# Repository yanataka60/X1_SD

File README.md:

# SHARP X1、X1turboにSD-CARDからロード、セーブ機能

　X1、X1turbo、X1turboZでSD-CARDからのアプリケーション起動とBASICなどのアプリケーションからSD-CARDへのロード、セーブを実現するものです。

　電源ONで起動するSD対応LauncherからはF又はLコマンドでSDからアプリケーションをLOAD実行ができます。

　LOAD実行範囲は、0000h～FF1Fhです。アプリケーション、ゲームを起動させるにはほぼ問題ないと思います。

　起動出来るのは、１段でロードできるCMTアプリケーションのみです。多段ロードで起動するCMTアプリケーションには対応していません。

　アプリケーション中でのSD-CARDとのロード、セーブについては、アプリケーションごとにSD-CARD対応化を行う必要があり、現在対応できているものは以下のとおりです。

|アプリケーション名|掲載誌|
| ------------ | ------------ |
|BASIC CZ-8CB01||
|S-OS SWORD TAPE版|Oh!MZ '86/2月号 '87/3,'89/2再掲載|
|TTLインタプリタ|Oh!MZ '84/10月号|
|EDAS for X1|月刊I/O '84/6月号|
|エディタ・アセンブラ|渡辺英行・沼倉　均共著「マシン語プログラミング入門」|
|Stellarコンパイラ|渡辺英行、高橋秀樹共著「X1ハイテックファイル」|

　X1turbo、X1turboZで利用するときは、RESOLUTIONスイッチを「STANDARD」にしてください。

　X1_SDはX1用アプリケーションを対象としており、X1_SD LauncherもX1用BASICからMONITOR部分を切り出して利用しています。

　なお、Arduino、ROMへ書き込むための機器が別途必要となります。

## 回路図
[X1_SD](https://github.com/yanataka60/X1_SD/blob/main/Kicad/X1_SD.pdf)

## 部品
|番号|品名|数量|備考|
| ------------ | ------------ | ------------ | ------------ |
||J2、J3のいずれか|||
|J2|Micro_SD_Card_Kit|1|秋月電子通商 AE-microSD-LLCNV (注1)|
|J3|MicroSD Card Adapter|1|Arduino等に使われる5V電源に対応したもの (注3)|
|J4|2x22Pinコネクタ|1|秋月電子通商 PH-2x40SGなど 拡張スロットの無いCZ-800に接続するときに必要です|
|J5|2x25Pinコネクタ|1|秋月電子通商 PH-2x40SGなど CZ-801に接続するときに必要です|
|J6|1x2Pinコネクタ|1|秋月電子通商 PH-1x40RG(2)など|
|R1、R2|1kΩ|2||
|U1|74LS04|1||
|U2|74LS30|1||
|U3|74LS10|1||
|U4、U7|74LS27|2||
|U5、U8|74LS273|2||
|U6、U9|74LS32|2||
|U10|74LS139|1||
|U11|74LS541|1||
|U12|8255|1||
|U13|27512/27C512相当品|1||
|U14|Arduino_Pro_Mini_5V|1|Atmega328版を使用 168版は不可。(注2)|
|C1、C3-C14|積層セラミックコンデンサ 0.1uF|6||
|C2|電解コンデンサ 16v100uF|1||
|S1|3Pスライドスイッチ|1|秋月電子通商 SS12D01G4など|
||ピンヘッダ|2Pin分|Arduino_Pro_MiniにはA4、A5用のピンヘッダが付いていないため別途調達が必要です 秋月電子通商 PH-1x40SGなど|
||ピンソケット(任意)|26Pin分|Arduino_Pro_Miniを取り外し可能としたい場合に調達します 秋月電子通商 FHU-1x42SGなど|
||2.54mmピッチ2x25Pinフラットケーブル|1|拡張スロットの無いCZ-800、CZ-801に接続するときに必要です(注4)|

　　　注1)秋月電子通商　AE-microSD-LLCNVのJ1ジャンパはショートしてください。

　　　注2)Arduino Pro MiniはA4、A5ピンも使っています。

　　　注3)Arduino等に使われる5V電源に対応したMicroSD Card Adapterも正しく信号を繋げば使えるとご報告いただきました。

　　　注4)拡張スロットの無いCZ-800に接続するときには本来2.54mmピッチ2x22Pinフラットケーブルですが、手に入りにくいので2.54mmピッチ2x25Pinフラットケーブルでも接続できます。CZ-801の接続には2.54mmピッチ2x25Pinフラットケーブルが必要です。

### MicroSD Card Adapterを使う
J3に取り付けます。

MicroSD Card Adapterについているピンヘッダを除去してハンダ付けするのが一番確実ですが、J3の穴にMicroSD Card Adapterをぴったりと押しつけ、裏から多めにハンダを流し込むことでハンダ付けをする方法もあります。なお、この方法の時にはしっかりハンダ付けが出来たかテスターで導通を確認しておいた方が安心です。

ハンダ付けに自信のない方はJ2の秋月電子通商　AE-microSD-LLCNVをお使いください。AE-microSD-LLCNVならパワーLED、アクセスLEDが付いています。

## ROMへの書込み
　まず、BASIC CZ-8CB01からIOCS(0000h～149Fh)を抜き出し、バイナリファイルとして保存します。

　CZ-8FB01 V10、CZ-8FB01 V20も大丈夫だとは思いますが、検証していません。なお、X1turbo用BASICは使えません。

　DumpList Editorを使ってWav又はtapファイルを読み込み、「マシン語入力に送る」を実行します。

　マシン語の14A0h以降を削除します。(0000h～149Fhのマシン語にします)

.jpg)

　「ファイル書出し」の「BIN(mot)ファイル書き出し(ヘッダ無し)(for他汎用)」を選択して「IOCS.bin」という名前で保存します。

.jpg)

　保存した「IOCS.bin」の後ろにバイナリエディタ等を使ってBOOTフォルダ内の「boot.bin」を付け加えます。0000h～17F6hのファイルとなるはずです。

　次にファイルの先頭に以下に示す32Byteのヘッダを付加します。0000h～1816hのファイルとなります。

　[0000] 01 58 31 5F 53 44 20 42 4F 4F 54 20 20 20 20 20

　[0010] 20 20 F7 17 00 00 00 00 20 20 20 20 20 20 00 00

.jpg)

　出来上がったら「X1_SD_BOOT.X1T」という名前で保存します。

　「X1_SD_BOOT.X1T」をROMライター(TL866II Plus等)を使って27512に書き込んでください。

### ROMにBOOT LOADERを書き込む方式の追加
　前述のBASICからMONITORを抜き出してROMに書き込む方式は、自分が所有しているBASICから抜き出してROMに書き込むには問題が無いのですが、書き込み済みROMの配布はSHARPの著作権があるので出来ません。

　そこで前述で作成した「X1_SD_BOOT.X1T」をSD-CARDから読み込み起動するプログラムをROMに書き込む方式を追加しました。

　前述「ROMへの書込み」の手順により作成した「X1_SD_BOOT.X1T」をそのファイルネームのままでSD-CARDに保存してください。

　次の手順でROMに書き込んだ「BOOT_LOADER.X1T」によりSD-CARD上の「X1_SD_BOOT.X1T」が自動的に読み込まれます。

#### BOOT LOADERをROMに書き込む
　BOOT_LOADERフォルダにある「BOOT_LOADER.X1T」をROMに書き込みます。

## Arduinoプログラム
　Arduino IDEを使ってArduinoフォルダ内のX1_SD.inoを書き込みます。

　SdFatライブラリを使用しているのでArduino IDEメニューのライブラリの管理からライブラリマネージャを立ち上げて「SdFat」をインストールしてください。

　「SdFat」で検索すれば見つかります。「SdFat」と「SdFat - Adafruit Fork」が見つかりますが「SdFat」のほうを使っています。

注)Arduinoを基板に直付けしている場合、Arduinoプログラムを書き込むときは、X1本体とは接続を外し、74LS04を外したうえで書き込んでください。

## 接続
### 拡張スロットが使える機体(拡張スロットのついたCZ-800、CZ-804、X1turbo等)の拡張スロットに差し込む
　X1_SD基板を拡張スロットに挿し込みます。

### 拡張スロットを装着していないCZ-800への接続
　X1本体のカバーを開けると拡張スロットを装着するためのコネクタがあるので以下の補助基板を挿し込むことでX1_SD基板とフラットケーブルで接続できるようになります。

.JPG)
.JPG)

#### 補助基板回路図
[X1_SD](https://github.com/yanataka60/X1_SD/blob/main/CZ-800_EXT-BOARD/CZ800EX.pdf)

#### 部品
|番号|品名|数量|備考|
| ------------ | ------------ | ------------ | ------------ |
|J2|2x22Pinコネクタ|1|秋月電子通商 PH-2x40SGなど|
||2.54mmピッチ2x22Pin又は2.54mmピッチ2x25Pinフラットケーブル|1||

J2の2x22Pinコネクタは基板裏側にハンダ付けします。

　本来2x22Pinのフラットケーブルでの接続ですが、手に入りにくいので2x25Pinフラットケーブルでも接続が可能です。

.JPG)

　補助基板はこのように挿し込みます。

.JPG)
.JPG)
.JPG)

　X1_SD基板側は、「for CZ-800」と表記のある2x22Pinコネクタにフラットケーブルを接続します。X1_SD基板への+5Vはフラットケーブルから供給されるので外部から供給する必要はありません。

.JPG)

### 外部拡張ユニット接続用拡張端子しかない機体(CZ-801等)に接続する場合
　拡張端子とX1_SDを2x25Pinフラットケーブルで接続します。

.JPG)

　拡張端子には+5Vが出ていないので外部からX1_SD基板へ+5Vを供給する必要があります。私は、プロッタプリンタのコネクタから取りました。右から3番目と4番目のピンが+5Vです。

.JPG)

　X1_SD基板側は、「for CZ-801C」と表記のある2x25Pinコネクタにフラットケーブルを接続します。本体から取り出した+5VはコネクタJ6に挿し込みます。J6は2Pinとも+5Vですのでどちらに挿し込んでも構いません。

.JPG)

　本体側の拡張端子にフラットケーブルを接続するときにはケーブルの折り返しが上に来るように接続してください。

.JPG)

　このように折り返しを下にして接続すると接触不良で正常に動作しないことがあります。

.JPG)

## SD-CARD
　出来れば8GB以下のSDカードを用意してください。

　ArduinoのSdFatライブラリは、SD規格(最大2GB)、SDHC規格(2GB～32GB)に対応していますが、SDXC規格(32GB～2TB)には対応していません。

　また、SDHC規格のSDカードであっても32GB、16GBは相性により動作しないものがあるようです。

　FAT16又はFAT32が認識できます。NTFSは認識できません。

　ルートに置かれたX1Tファイルのみ認識できます。(X1T以外のファイル、フォルダも表示されますがLOAD実行の対象になりません)

　ファイル名は「.X1T」を除いて32文字まで、ただし半角カタカナ、及び一部の記号はArduinoが認識しないので使えません。パソコンでファイル名を付けるときはアルファベット、数字および空白でファイル名をつけてください。

## X1Tファイルの作成
　X1エミュレータ用CMTファイルはTAP形式が一般的ですが、X1_SDではマシン語にヘッダ(FCB)を付加したバイナリファイルを扱い、拡張子をX1Tとしています。

　ヘッダ(FCB)の構造

|アドレス|内容|説明|
| ------------ | ------------ | ------------ |
|00|モード|01:マシン語,02:BASIC,03:ASC,04:その他|
|01～0D|ファイル名|13文字分|
|0E～10|拡張子|3文字|
|11|パスワード|無指定時は20h|
|12～13|データ長||
|14～15|データ先頭アドレス||
|16～17|実行アドレス||
|18～1C|ファイル作成年月日|無指定時は20h|
|1D～1F|システム格納アドレス|CMT,X1_SDの場合は00h,00h,00h|

### X1T作成例(サンダーフォースをX1Tファイル化)
　1) DumpListEditorを起動し、対象マシンとして「X1」を選択

　2)サンダーフォースのWav又はTapファイルをDumpListEditorにドロップする。

.jpg)

　3)「マシン語入力に送る」をクリックするとマシン語入力画面に切り替わる。

.jpg)

　4)ここで表示される以下の３つの情報をメモします。

// PROG AREA = 0000-FEFF

// PROG SIZE = FF00 (65280BYTE)

// EXEC ADRS = 0000

　5)「ファイル書出し」の「BIN(mot)ファイル書き出し(ヘッダ無し)(for他汎用)」を選択して適当な名前(例 THUNDER FORCE.bin)で保存します。

.jpg)

　6)保存したファイル(例 THUNDER FORCE.bin)をバイナリエディタ等で開き、先程のFCBの構造に基づいて32Byteのヘッダを付加し、拡張子をX1Tとし適当な名前(例 THUNDER FORCE.X1T)を付けて保存します。

.jpg)

　7)SDカードにコピーします。

　8)他のアプリケーションも同様にX1TファイルにしてSDカードにコピーしてください。ただし、起動可能なアプリケーションは機械語で１段ロードの物に限ります。

　9)雑誌等に掲載されたアプリケーション、ゲーム等でIOCSを必要とするものはIOCSも含めたX1Tファイルを作るか、X1_SD対応BASIC CZ-8CB01を起動してから当該アプリケーション、ゲームを起動してください。

## 操作方法
　電源ON、又はリセットでX1_SD Launcherのコマンド入力待ちになるので以下のコマンドが使えます。

　X1のMONITORで使えるD,M,G,Tコマンドは同じように使えます。

　X1の起動プロセスは、FDD、ROM、CMTの順です。X1_SDを装着したままCMTからLOADしたい場合は、Cキーを押したままで電源ON、又はリセットしてください。

　以下、SD-CARD内のファイルに付けられるファイル名をDOSファイル名、X1T形式ファイルのFCB内ファイル名をFCBファイル名とします。

### L　DOSファイル名[CR]
　DOSファイル名で指定したバイナリファイルをLOADして実行します。

　「.X1T」は省略可能です。

　LとDOSファイル名の間に空白が有っても無くても構いません。また、空白はいくつあっても構いません。

　LOAD実行可能範囲は0000h～FF1Fhです。

　なお、LOADするアプリケーションのLOAD範囲外のメインRAMは最少のSDアクセスルーチン(FF20h～FF7Dh)以外ゼロ埋めクリアされます。Launcherも消去されるのでIOCSを使用するアプリケーションをLOADしたい場合はIOCSを連結してLOADしてください。

例)

*L　TEST[CR]

*L　TEST.x1t[CR]

*LTEST[CR]

*L　　TEST[CR]

### F[CR]
　SD-CARDルートディレクトリにあるファイルの一覧を表示します。20件表示したところで指示待ちになるので打ち切るならESC、SHIFT+BREAK又は↑を入力すると打ち切られ、Bキーで前の20件に戻ります。それ以外のキーで次の20件を表示します。

　行頭に「*L」を付加して表示してあるので実行したいファイルにカーソルキーを合わせて[CR]キーを押すだけでLOAD、実行が可能です。

　表示される順番は、登録順となりファイル名アルファベッド順などのソートした順で表示することはできません。

　LOAD実行可能範囲は0000h～FF1Fhです。

### F　x[CR]
ファイル名がxで始まるファイルの一覧を表示します。20件表示したところで指示待ちになるので打ち切るならESC、SHIFT+BREAK又は↑を入力すると打ち切られ、Bキーで前の20件に戻ります。それ以外のキーで次の20件を表示します。

xはX1のキーボードから入力可能な32文字までの文字列です。(数字、記号、アルファベット)

　Fとxの間に空白が有っても無くても構いません。また、空白はいくつあっても構いません。

　LOAD実行可能範囲は0000h～FF1Fhです。

例)

*F　S[CR]

*F　SP[CR]

*F　BASIC S[CR]

*FS[CR]

*F　　S[CR]

### アプリケーションからのLOAD
　L、LOAD等アプリケーションが指定したコマンドの後ろにはFCBファイル名を指定可となっていますが、指定せずにL、LOAD等のコマンドのみで[CR]キーを押します。

　CMTの場合にはここでPLAYボタンを押すよう指示が出るところですが、「DOS FILE:」と表示して行入力待ちになっているのでDOSファイル名を入力して[CR]キーを押します。この時、「.X1T」の入力は省略できます。

　DOSファイル名は「.X1T」を除いて32文字まで、ただし半角カタカナ、及び一部の記号はArduinoが認識しないので使えません。パソコンでファイル名を付けるときはアルファベット、数字および空白でファイル名をつけてください。

例)BASIC CZ-8CB01では

× LOAD "TEST"[CR]

○ LOAD[CR]

　DOS FILE:TEST[CR]

○ LOAD[CR]

　DOS FILE:TEST.X1T[CR]

** 参考 **

　S-OS SWORDでの運用に当たっては起動直後に「DV S:」としてデバイスを各SYSTEMデバイスとしてください。

　FUZZY BASICだけかもしれませんが共通フォーマットデバイスのままだとLOADコマンドでFCBファイル名の省略ができませんでした。

#### LOAD時の特殊コマンド
　「DOS FILE:」と表示して行入力待ちになったときに以下の特殊コマンドが使用可能です。

##### *F[CR]
##### *F x[CR]
　Launcherコマンド入力待ちからのF、F xと全く同等のファイル一覧機能が使えます。

　検索結果の行頭には「DOS FILE:」を付加して表示してあるのでLOADしたいファイルにカーソルキーを合わせて[CR]キーを押すだけでLOADが可能です。

### アプリケーションからのSAVE
　CMTの時と同様にアプリケーションの指定する入力方法、ルールでファイル名等を入力して保存してください。

　ただし、半角カタカナはArduinoが認識できないため、使用できません。アルファベット、数字および空白で指定してください。

　SAVE時は、入力したファイル名がFCBファイル名、DOSファイル名の両方に適用されます。

　DOSファイル名としての「.X1T」は自動的に付加されます。

例)BASIC CZ-8CB01では

○ SAVE "TEST"[CR]

## 操作上の注意
　~~「SD-CARD INITIALIZE ERROR」と表示されたときは、SD-CARDをいったん抜き再挿入したうえでArduinoをリセットしてください。~~

　~~SD-CARDにアクセスしていない時に電源が入ったままで SD-CARDを抜いた後、再挿入しSD-CARDにアクセスすると「SD-CARD INITIALIZE ERROR」となる場合があります。再挿入した場合にはSD-CARDにアクセスする前にArduinoを必ずリセットしてください。~~

　~~SD-CARDの抜き差しは電源を切った状態で行うほうがより確実です。~~

　(2024.3.13) SD-CARDにアクセスしていない時に電源が入ったままでSD-CARDを抜くと再度SD-CARDを挿入してもSD-CARDにアクセスできない問題を解消しました。(Arduinoを最新版に書き換えてください)

　再度SD-CARDを挿入した後、Fコマンド、Lコマンド、LOAD、SAVE等でSD-CARDに3回ほどアクセスすれば復旧します。

## アプリケーションからSD-CARDとのLOAD、SAVEをするための対応
### BASIC CZ-8CB01
　BASIC CZ-8CB01にSDアクセス用ルーチンを付加してX1Tファイルを作成します。

　ROMへの書込みの為にBASIC CZ-8CB01をバイナリファイルとしたのと同様の操作をしてBASIC CZ-8CB01のバイナリファイルを作成します。

　DumpList Editorを使ってWav又はtapファイルを読み込み、「マシン語入力に送る」を実行します。

.jpg)

　PROG AREAは、0000-9E0Fとなっていると思います。

　「ファイル書出し」の「BIN(mot)ファイル書き出し(ヘッダ無し)(for他汎用)」を選択して「CZ-8CB01.bin」という名前で保存します。

　保存した「CZ-8CB01.bin」の後ろにバイナリエディタ等を使ってSD_ACCESS_BASIC_CZ-8CB01フォルダ内の「SD_ACCESS_BASIC_CZ-8CB01.bin」を付け加えます。0000h～A267hのファイルとなるはずです。

　次にファイルの先頭に以下に示す32Byteのヘッダを付加します。0000h～A287hのファイルとなります。

　なお、実行開始アドレスは、9E10hです。

　[0000] 01 42 41 53 49 43 20 43 5A 38 43 42 30 31 20 20

　[0010] 20 20 68 A2 00 00 10 9E 20 20 20 20 20 20 00 00

.jpg)

　出来上がったら「BASIC CZ8CB01_SD.X1T」という名前で保存し、SDカードにコピーします。

　Launcherから「BASIC CZ8CB01_SD.X1T」を選択してロードするとX1_SD対応BASIC CZ8CB01が起動します。

　起動直後に必ずCLEAR &HF800又はLIMIT &HF800を実行してください。SDカードアクセスルーチンはF800h～FC9Fhに配置されています。

　SAVEコマンドにAオプションをつけることでアスキー形式でのSAVEも出来ますが、SAVE、LOADに非常に時間が掛かります。気長にお待ちください。

#### DumpListEditorで入力したBASICプログラムをX1T形式に変換する方法
　DumpListEditorを使えばWindowsパソコンでBASIC CZ-8CB01用のBASICプログラムが入力できますが、保存方法がテキスト形式又はTAP形式のみでそのままX1T形式で保存することが出来ません。

　以下の方法でX1T形式に変換してください。

　OCRからの変換、キーボードからの入力等でBASICプログラムを入力します。

.jpg)

　「ファイル整理画面にPaste」をクリックしてファイル整理画面に送ります。

.jpg)

　「マシン語入力に送る」をクリックしてマシン語入力画面に送ります。

.jpg)

　ここで表示される「PROG SIZE」を控えておきます。

　「ファイル書出し」の「BIN(mot)ファイル書き出し(ヘッダ無し)(for他汎用)」を選択し任意のファイル名で保存します。

　バイナリエディタ等を使って保存したファイルを読み込み、先頭に以下に示す32Byteのヘッダを付加して保存します。

|アドレス|内容|説明|
| ------------ | ------------ | ------------ |
|00|モード|02h|
|01～0D|ファイル名|13文字分|
|0E～10|拡張子|3文字|
|11|パスワード|20h|
|12～13|データ長|PROG SIZEで表示されたサイズの上位、下位を逆にします|
|14～15|0000h||
|16～17|0000h||
|18～1C|ファイル作成年月日|20h|
|1D～1F|システム格納アドレス|00h,00h,00h|

例)

.jpg)

#### なお、今のところ、X1T形式で保存されたBASICプログラムをDumpListEditorで編集する方法はありません。

### S-OS SWORD
　Oh!MZ '86/2月号に掲載されたS-OS SWORDをX1_SD対応とすることでOh!MZ誌及びOh!X誌に連載されたTHE SENTINELのプログラムがFDD、CMT無しでも利用できるようになります。

　Oh!MZ誌掲載のダンプリストから入力したテープ専用版SWORDが必要ですが、大石様のWEB THE SENTINEL http://www.retropc.net/ohishi/s-os/ からsword.binがダウンロードできます。『X1/C/D/Cs/Ck/F/G/Twin (1986.2,1987.3,1989.2)』版をダウンロードしてください。

　ダウンロードしたX1Sword-1989-02.zipを解凍するとbinariesフォルダにsword.bin(6,101Byte)があります。

　まず、sword.binに以下のパッチを当て、テープ専用版に修正します。

|ADDRESS|実ADDRESS|修正前|修正後|
| ------------ | ------------ | ------------ | ------------ |
|0AA6|1FA6|C3 4F 23|C3 37 1C|
|0AA9|1FA9|C3 7C 23|C3 32 1C|
|0AAC|1FAC|C3 2D 23|C3 2D 1C|
|0AAF|1FAF|C3 B3 22|C3 28 1C|
|0B00|2000|C3|C9|
|0B03|2003|C3|C9|
|0B06|2006|C3 19 24|C3 73 1B|
|0B09|2009|C3 FA 22|C3 18 1B|
|0B0C|200C|C3|C9|
|0B0F|200F|C3|C9|
|0B12|2012|C3|C9|
|0B15|2015|C3|C9|

　修正が終わったら1600h(実アドレス2B00h)以降は、ディスクI/Oで必要ありませんので0000h～15FFhまでを保存します。

　BASIC CZ-8CB01から抜き出したIOCS(0000h～149Fh)、テープ専用版sword.bin(1500h～2AFFh)、SD_ACCESS_SOS_SWORDフォルダ内の「SD_ACCESS_SOS_SWORD.bin」(2B00h～2F38h)の3つをバイナリエディタ等を使ってIOCS、sword.bin、SD_ACCESS_SOS_SWORD.binの順番に連結します。IOCSの後ろの14A0h～1AFFhまでは00hで埋めてください。

　0000h～2F38hのファイルとなります。

　次にファイルの先頭に以下に示す32Byteのヘッダを付加します。0000h～2F58hのファイルとなります。

　なお、実行開始アドレスは、2B00hです。

　[0000] 01 53 2D 4F 53 20 53 57 4F 52 44 5F 53 44 20 20

　[0010] 20 20 39 2F 00 00 00 2B 20 20 20 20 20 20 00 00

　出来上がったら「SWORD_SD.X1T」という名前で保存し、SDカードにコピーします。

　S-OS SWORD起動直後に「DV S:」としてSYSTEMデバイスに切り替えておいた方が無難です。なお、SDカードアクセスルーチンはF800h～FC80hに配置されます。

　S-OS用のアプリケーションも大石様のWEB THE SENTINEL http://www.retropc.net/ohishi/s-os/ からダウンロードできます。

　公開されているアプリケーションの多くは、obj形式となっていますのでX1T形式のヘッダに付け替えます。

　先頭の10Byteがobj形式のヘッダですので削除し、32Byteのヘッダを付加してX1T形式にしたうえでSDカードにコピーします。

例)INVADER GAME (1987.4)

.jpg)

.jpg)

### C-GRACE
　徳間書店発行のテクノポリスに掲載されたC-GRACE用にLauncherを作ってみました。

　BASIC CZ-8CB01から抜き出したIOCS(0000h～149Fh)、SD_ACCESS_C-GRACEフォルダ内の「SD_ACCESS_C-GRACE.bin」(14A0h～5FFFh)、C-GRACE Executerのバイナリファイル(6000h～7FFFh)を用意します。

　バイナリエディタ等を使って3つのファイルをIOCS、SD_ACCESS_C-GRACE.bin、C-GRACE Executerの順番に連結します。0000h～7FFFhのファイルとなるはずです。

　次にファイルの先頭に以下に示す32Byteのヘッダを付加します。0000h～801Fhのファイルとなります。

　なお、実行開始アドレスは、0000hです。

　[0000] 01 43 2D 47 52 41 43 45 20 20 20 20 20 20 20 20

　[0010] 20 20 00 80 00 00 00 00 20 20 20 20 20 20 00 00

.jpg)

　出来上がったら「C-GRACE_SD.X1T」という名前で保存し、SDカードにコピーします。

　C-GRACE用のデータも32Byteのヘッダを付加してX1T形式にしたうえでSDカードにコピーします。

|アドレス|内容|説明|
| ------------ | ------------ | ------------ |
|00|モード|01h|
|01～0D|ファイル名|13文字分|
|0E～10|拡張子|3文字|
|11|パスワード|20h|
|12～13|データ長|各データのファイルサイズによる|
|14～15|データ先頭アドレス|00h,20h|
|16～17|実行アドレス|6000h|
|18～1C|ファイル作成年月日|20h|
|1D～1F|システム格納アドレス|00h,00h,00h|

.jpg)

　Launcherから「C-GRACE_SD.X1T」を選択してロードするとC-GRACE Launcherが起動します。

　C-GRACE LauncherからFコマンド、LコマンドでC-GRACEデータファイルを選択して読み込みます。

　CGの描画が終わるとキー入力待ちになるので何かキーを押すとグラフィック画面が消えて、C-GRACE Launcherのコマンド待ちに戻ります。

### TTLインタプリタ
　Oh!MZ '84/10月号に掲載されたTTLインタプリタです。

　BASIC CZ-8CB01から抜き出したIOCS(0000h～149Fh)、SD_ACCESS_TTLフォルダ内の「SD_ACCESS_TTL.bin」(14A0h～192Eh)、TTLインタプリタのオブジェクト(B000h～BBFFh)の3つをバイナリエディタ等を使ってIOCS、SD_ACCESS_TTL.bin、TTLインタプリタのオブジェクトの順番に連結します。TTLインタプリタのオブジェクトはSD_ACCESS_TTL.binの直後(192Fh～)に連結します。

　0000h～252Ehのファイルとなります。

　次にファイルの先頭に以下に示す32Byteのヘッダを付加します。0000h～254Ehのファイルとなります。

　なお、実行開始アドレスは、14A0hです。

　[0000] 01 54 54 4C 2D 58 31 5F 53 44 20 20 20 20 20 20

　[0010] 20 20 2F 25 00 00 A0 14 20 20 20 20 20 20 00 00

　出来上がったら「TTL-X1_SD.X1T」という名前で保存し、SDカードにコピーします。

　なお、SDカードアクセスルーチンは14A0h～192Ehに配置されます。

### EDAS for X1
　月刊I/O '84/6月号に掲載されたEDAS for X1です。

　BASIC CZ-8CB01から抜き出したIOCS(0000h～149Fh)、EDAS for X1のオブジェクト(14A0h～34FFh)、SD_ACCESS_EDASフォルダ内の「SD_ACCESS_EDAS.bin」(3500h～3945h)の3つをバイナリエディタ等を使ってIOCS、EDAS for X1のオブジェクト、SD_ACCESS_EDAS.binの順番に連結します。

　0000h～3945hのファイルとなります。

　次にファイルの先頭に以下に示す32Byteのヘッダを付加します。0000h～254Ehのファイルとなります。

　なお、実行開始アドレスは、3500hです。

　[0000] 01 45 44 41 53 5F 58 31 5F 53 44 20 20 20 20 20

　[0010] 20 20 46 39 00 00 00 35 20 20 20 20 20 20 00 00

　出来上がったら「EDAS_X1_SD.X1T」という名前で保存し、SDカードにコピーします。

　なお、SDカードアクセスルーチンはF800h～FC8Dhに配置されます。

### X1エディタ・アセンブラ
　渡辺英行・沼倉　均共著「マシン語プログラミング入門」に掲載されたエディタ・アセンブラです。

　BASIC CZ-8CB01から抜き出したIOCS(0000h～149Fh)、エディタ・アセンブラのオブジェクト(14A0h～4A9Fh)、SD_ACCESS_X1_EDITOR_ASSEMBLERフォルダ内の「SD_ACCESS_X1_EDITOR_ASMBLR.bin」(4AA0h～4ECDh)の3つをバイナリエディタ等を使ってIOCS、エディタ・アセンブラのオブジェクト、SD_ACCESS_X1_EDITOR_ASMBLR.binの順番に連結します。

　0000h～4ECDhのファイルとなります。

　次にファイルの先頭に以下に示す32Byteのヘッダを付加します。0000h～4EEDhのファイルとなります。

　なお、実行開始アドレスは、4AA0hです。

　[0000] 01 58 31 5F 45 44 20 41 53 53 45 4D 42 4C 20 20

　[0010] 20 20 CE 4E 00 00 A0 4A 20 20 20 20 20 20 00 00

　出来上がったら「X1_EDITOR_ASSEMBLER_SD.X1T」という名前で保存し、SDカードにコピーします。

　なお、SDカードアクセスルーチンはF800h～FC75hに配置されます。

### Stellarコンパイラ
　渡辺英行、高橋秀樹共著「X1ハイテックファイル」に掲載されたStellarコンパイラです。

　BASIC CZ-8CB01から抜き出したIOCS(0000h～149Fh)、Stellarコンパイラのオブジェクト(14A0h～67DFh)、SD_ACCECC_STELLARフォルダ内の「SD_ACCESS_STELLAR.bin」(67E0h～6C1Ah)の3つをバイナリエディタ等を使ってIOCS、Stellarコンパイラのオブジェクト、SD_ACCESS_STELLAR.binの順番に連結します。

　0000h～6C1Ahのファイルとなります。

　次にファイルの先頭に以下に示す32Byteのヘッダを付加します。0000h～6C3Ahのファイルとなります。

　なお、実行開始アドレスは、67E0hです。

　[0000] 01 53 74 65 6C 6C 61 72 5F 53 44 20 20 20 20 20

　[0010] 20 20 1B 6C 00 00 E0 67 20 20 20 20 20 20 00 00

　出来上がったら「Stellar_SD.x1t」という名前で保存し、SDカードにコピーします。

　なお、SDカードアクセスルーチンはAB7Dh～AFFFhに配置されます。

## 謝辞
　基板の作成に当たり以下のデータを使わせていただきました。ありがとうございました。

　Arduino Pro Mini

　　https://github.com/g200kg/kicad-lib-arduino

　AE-microSD-LLCNV

　　https://github.com/kuninet/PC-8001-SD-8kRAM

　ドキュメントの誤りを発見していただきました、ゆうじろう様。ありがとうございました。

## 追記
2023.10.26　SD対応アプリケーションにStellarコンパイラを追加。

2023.10.26　BASIC CZ-8CB01からSD-CARDとのLOAD、SAVEをするための対応の説明中のヘッダに誤りがありました。

2023.12.25　BASICから抽出したMONITORを修正して作成したX1_SD_BOOT.X1TをROMに書き込む方式以外にX1_SD_BOOT.X1TをSD-CARDから読み込むプログラムをROMに書き込む方式を追加した。

2024.1.15　SDカードは8GB以下が望ましいことを追記。

2024.1.26　BOOT LOADERのバグを修正。

2024.3.13　電源が入ったままでSD-CARDを抜くと再度SD-CARDを挿入してもSD-CARDにアクセスできない問題を解消した。

2025.12.4　kuran_kuranさんにArduinoプログラムのバグを発見していただきました。精査した結果、不要な処理が含まれていることが原因であったため不要な処理部分を削除しました。なお、未修正のままでも実害はありません。kuran_kuranさん、ありがとうございました。

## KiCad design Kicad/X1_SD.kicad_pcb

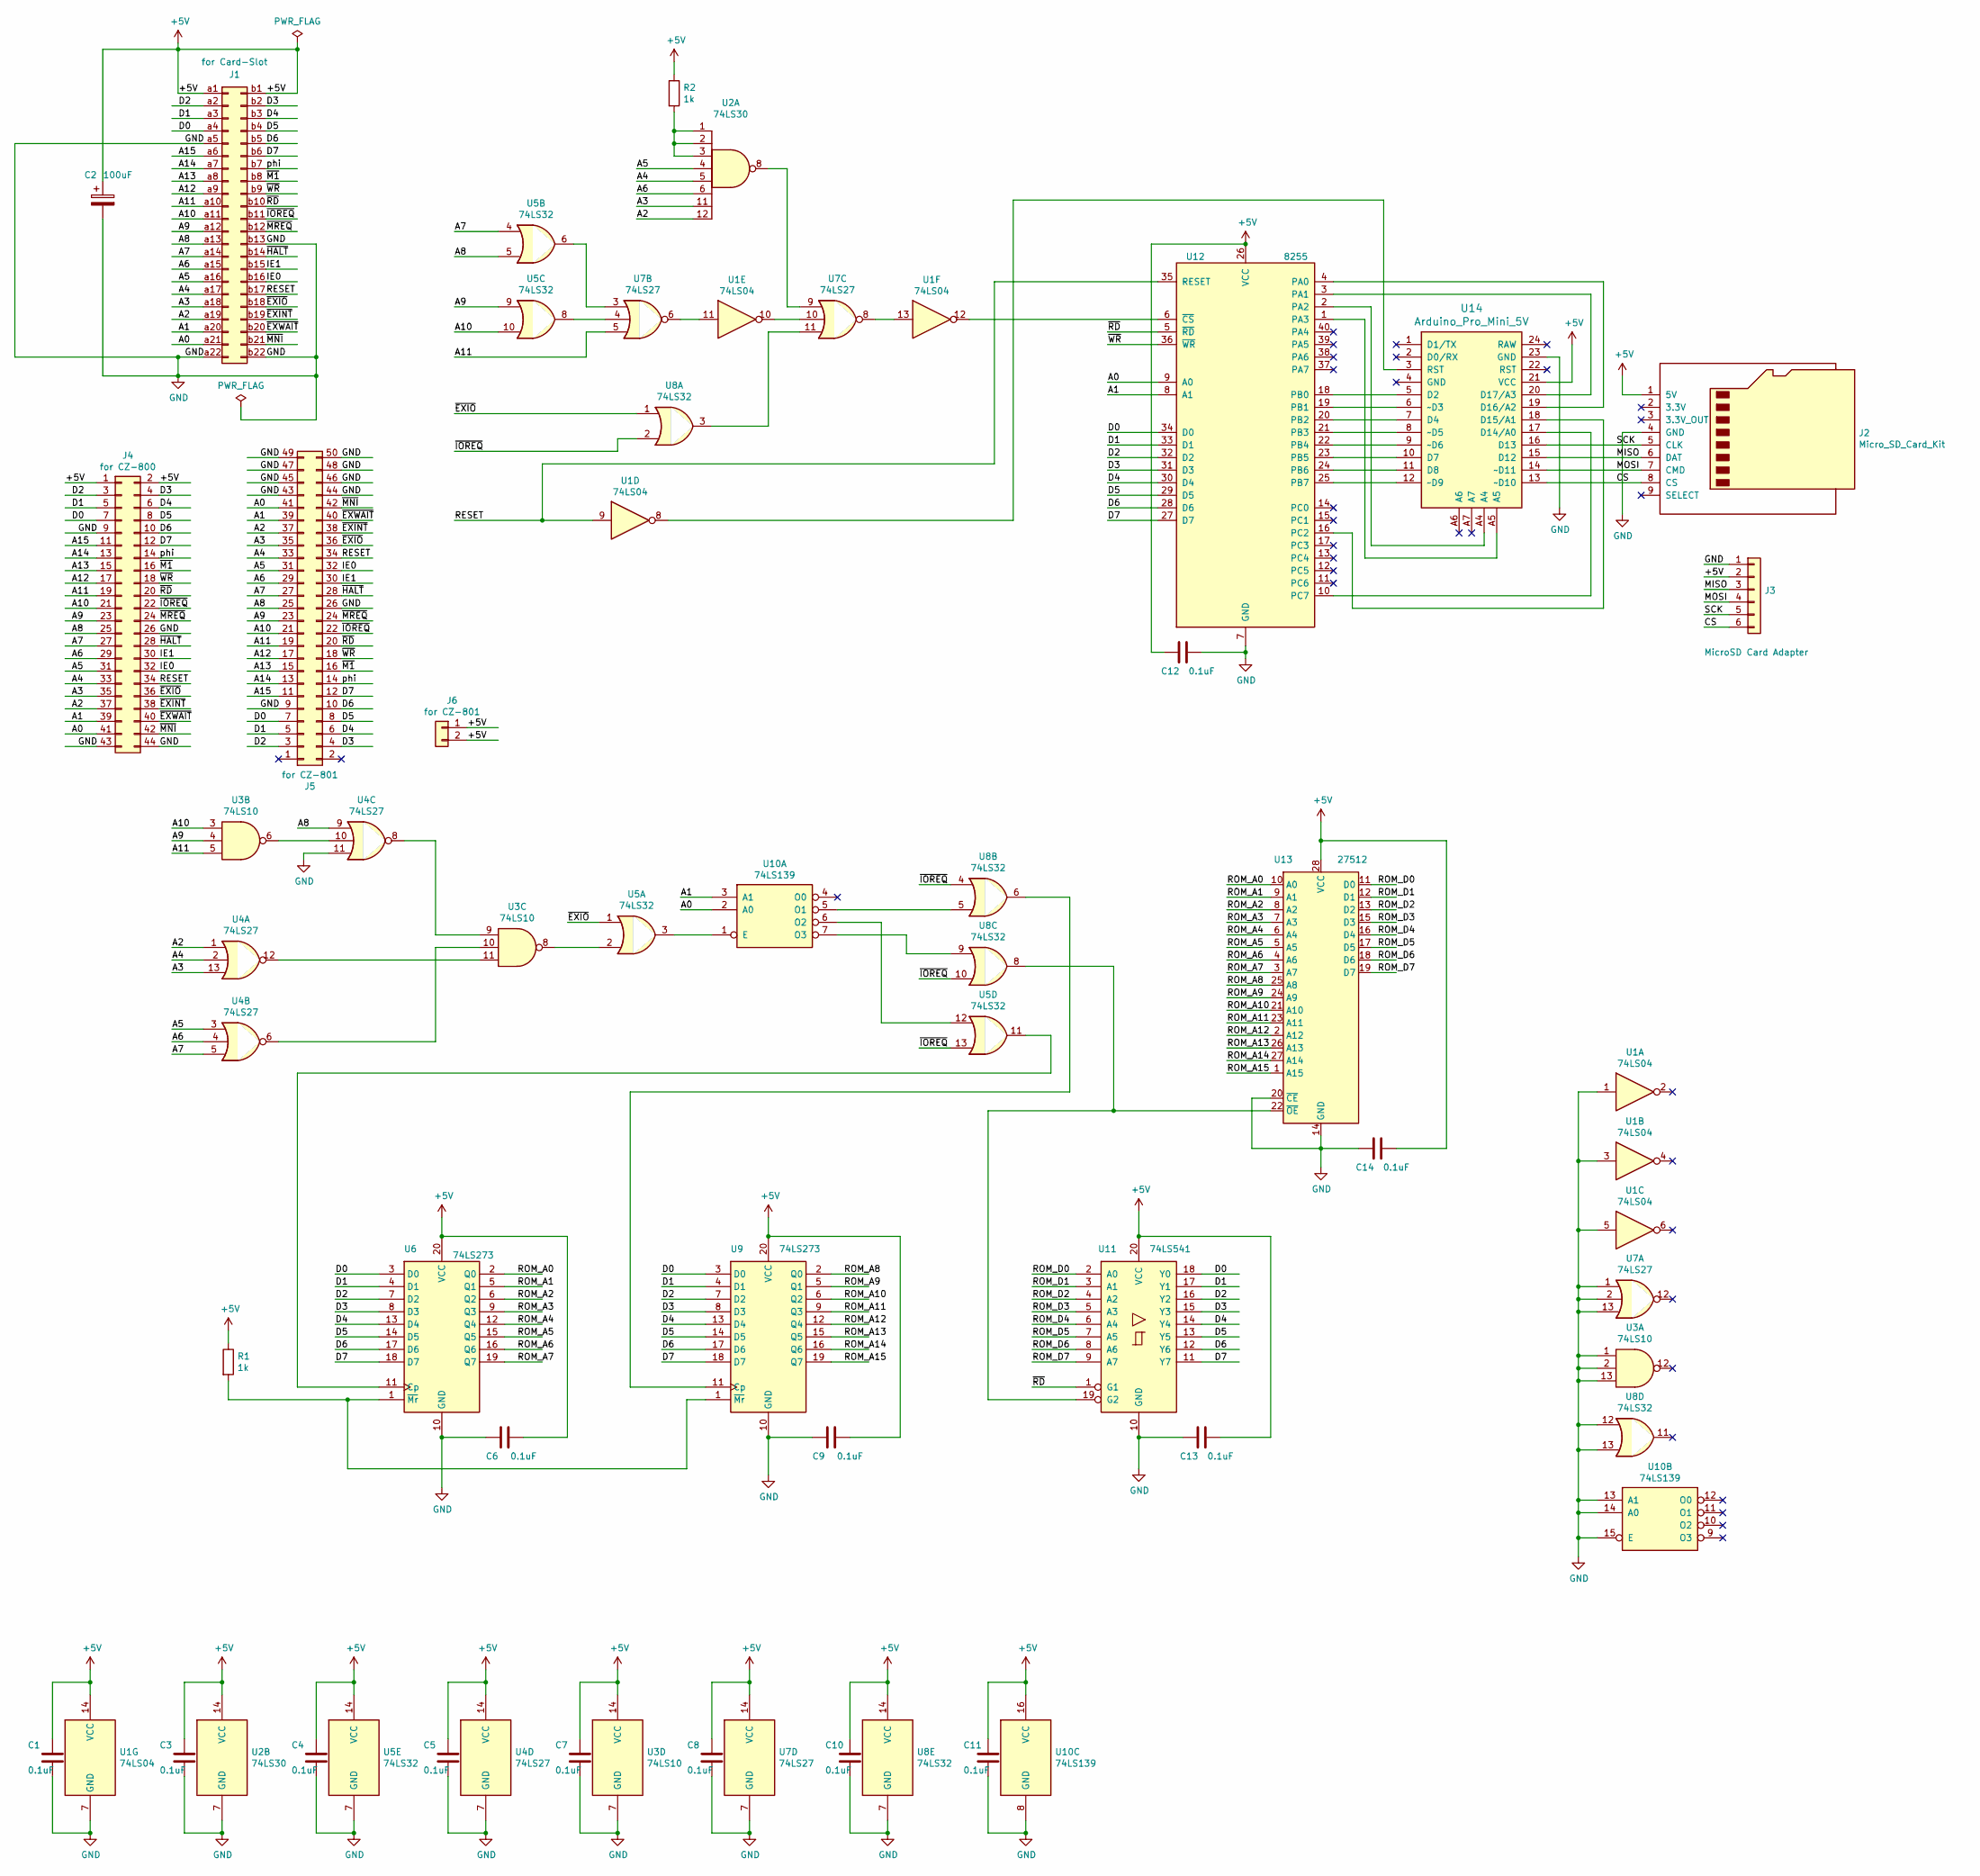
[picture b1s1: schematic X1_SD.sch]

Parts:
C1, C3, C4, C5, C6, C7, C8, C9, C10, C11, C12, C13, C14: 0.1uF; C_Rect_L4.0mm_W2.5mm_P2.50mm
C2: 100uF; CP_Radial_D5.0mm_P2.50mm
J1: for Card-Slot; BUS_MZ2000
J2: Micro_SD_Card_Kit; AE-microSD-LLCNV
J3: MicroSD Card Adapter; PinSocket_1x06_P2.54mm_Vertical
J4: for CZ-800; PinHeader_2x22_P2.54mm_Vertical
J5: for CZ-801; PinHeader_2x25_P2.54mm_Vertical
J6: for CZ-801; PinHeader_1x02_P2.54mm_Horizontal
R1, R2: 1k; R_Axial_DIN0207_L6.3mm_D2.5mm_P7.62mm_Horizontal
U1: 74LS04; DIP-14_W7.62mm_LongPads
U2: 74LS30; DIP-14_W7.62mm_LongPads
U3: 74LS10; DIP-14_W7.62mm_LongPads
U4, U7: 74LS27; DIP-14_W7.62mm_LongPads
U5, U8: 74LS32; DIP-14_W7.62mm_LongPads
U6, U9: 74LS273; DIP-20_W7.62mm_LongPads
U10: 74LS139; DIP-16_W7.62mm_LongPads
U11: 74LS541; DIP-20_W7.62mm_LongPads
U12: 8255; DIP-40_W15.24mm_LongPads
U13: 27512; DIP-28_W15.24mm_LongPads
U14: Arduino_Pro_Mini_5V; Arduino_Pro_Mini

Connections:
+5V: C1.1, C2.1, C3.1, C4.1, C5.1, C6.2, C7.1, C8.1, C9.2, C10.1, C11.1, C12.1, C13.2, C14.2, J1.a1, J1.b1, J2.1 (5V), J3.2, J4.1, J4.2, J6.1, J6.2, R1.1, R2.1, U1.14 (VCC), U2.14 (VCC), U3.14 (VCC), U4.14 (VCC), U5.14 (VCC), U6.20 (VCC), U7.14 (VCC), U8.14 (VCC), U9.20 (VCC), U10.16 (VCC), U11.20 (VCC), U12.26 (VCC), U13.28 (VCC), U14.21 (VCC)
/A0: J1.a21, J4.41, J5.41, U10.2 (A0), U12.9 (A0)
/A1: J1.a20, J4.39, J5.39, U10.3 (A1), U12.8 (A1)
/A2: J1.a19, J4.37, J5.37, U2.12, U4.1
/A3: J1.a18, J4.35, J5.35, U2.11, U4.13
/A4: J1.a17, J4.33, J5.33, U2.5, U4.2
/A5: J1.a16, J4.31, J5.31, U2.4, U4.3
/A6: J1.a15, J4.29, J5.29, U2.6, U4.4
/A7: J1.a14, J4.27, J5.27, U4.5, U5.4
/A8: J1.a13, J4.25, J5.25, U4.9, U5.5
/A9: J1.a12, J4.23, J5.23, U3.4, U5.9
/A10: J1.a11, J4.21, J5.21, U3.3, U5.10
/A11: J1.a10, J4.19, J5.19, U3.5, U7.5
/A12: J1.a9, J4.17, J5.17
/A13: J1.a8, J4.15, J5.15
/A14: J1.a7, J4.13, J5.13
/A15: J1.a6, J4.11, J5.11
/CS: J2.8 (CS), J3.6, U14.13 (~~D10)
/D0: J1.a4, J4.7, J5.7, U6.3 (D0), U9.3 (D0), U11.18 (Y0), U12.34 (D0)
/D1: J1.a3, J4.5, J5.5, U6.4 (D1), U9.4 (D1), U11.17 (Y1), U12.33 (D1)
/D2: J1.a2, J4.3, J5.3, U6.7 (D2), U9.7 (D2), U11.16 (Y2), U12.32 (D2)
/D3: J1.b2, J4.4, J5.4, U6.8 (D3), U9.8 (D3), U11.15 (Y3), U12.31 (D3)
/D4: J1.b3, J4.6, J5.6, U6.13 (D4), U9.13 (D4), U11.14 (Y4), U12.30 (D4)
/D5: J1.b4, J4.8, J5.8, U6.14 (D5), U9.14 (D5), U11.13 (Y5), U12.29 (D5)
/D6: J1.b5, J4.10, J5.10, U6.17 (D6), U9.17 (D6), U11.12 (Y6), U12.28 (D6)
/D7: J1.b6, J4.12, J5.12, U6.18 (D7), U9.18 (D7), U11.11 (Y7), U12.27 (D7)
/IE0: J1.b16, J4.32, J5.32
/IE1: J1.b15, J4.30, J5.30
/MISO: J2.6 (DAT), J3.3, U14.15 (D12)
/MOSI: J2.7 (CMD), J3.4, U14.14 (~~D11)
/RESET: J1.b17, J4.34, J5.34, U1.9, U12.35 (RESET)
/ROM_A0: U6.2 (Q0), U13.10 (A0)
/ROM_A1: U6.5 (Q1), U13.9 (A1)
/ROM_A2: U6.6 (Q2), U13.8 (A2)
/ROM_A3: U6.9 (Q3), U13.7 (A3)
/ROM_A4: U6.12 (Q4), U13.6 (A4)
/ROM_A5: U6.15 (Q5), U13.5 (A5)
/ROM_A6: U6.16 (Q6), U13.4 (A6)
/ROM_A7: U6.19 (Q7), U13.3 (A7)
/ROM_A8: U9.2 (Q0), U13.25 (A8)
/ROM_A9: U9.5 (Q1), U13.24 (A9)
/ROM_A10: U9.6 (Q2), U13.21 (A10)
/ROM_A11: U9.9 (Q3), U13.23 (A11)
/ROM_A12: U9.12 (Q4), U13.2 (A12)
/ROM_A13: U9.15 (Q5), U13.26 (A13)
/ROM_A14: U9.16 (Q6), U13.27 (A14)
/ROM_A15: U9.19 (Q7), U13.1 (A15)
/ROM_D0: U11.2 (A0), U13.11 (D0)
/ROM_D1: U11.3 (A1), U13.12 (D1)
/ROM_D2: U11.4 (A2), U13.13 (D2)
/ROM_D3: U11.5 (A3), U13.15 (D3)
/ROM_D4: U11.6 (A4), U13.16 (D4)
/ROM_D5: U11.7 (A5), U13.17 (D5)
/ROM_D6: U11.8 (A6), U13.18 (D6)
/ROM_D7: U11.9 (A7), U13.19 (D7)
/SCK: J2.5 (CLK), J3.5, U14.16 (D13)
/phi: J1.b7, J4.14, J5.14
/~EXINT: J1.b19, J4.38, J5.38
/~EXIO: J1.b18, J4.36, J5.36, U5.1, U8.1
/~EXWAIT: J1.b20, J4.40, J5.40
/~HALT: J1.b14, J4.28, J5.28
/~IOREQ: J1.b11, J4.22, J5.22, U5.13, U8.2, U8.4, U8.10
/~M1: J1.b8, J4.16, J5.16
/~MNI: J1.b21, J4.42, J5.42
/~MREQ: J1.b12, J4.24, J5.24
/~RD: J1.b10, J4.20, J5.20, U11.1 (G1), U12.5 (~RD~)
/~WR: J1.b9, J4.18, J5.18, U12.36 (~WR~)
GND: C1.2, C2.2, C3.2, C4.2, C5.2, C6.1, C7.2, C8.2, C9.1, C10.2, C11.2, C12.2, C13.1, C14.1, J1.a5, J1.a22, J1.b13, J1.b22, J2.4 (GND), J3.1, J4.9, J4.26, J4.43, J4.44, J5.9, J5.26, J5.43, J5.44, J5.45, J5.46, J5.47, J5.48, J5.49, J5.50, U1.1, U1.3, U1.5, U1.7 (GND), U2.7 (GND), U3.1, U3.2, U3.7 (GND), U3.13, U4.7 (GND), U4.11, U5.7 (GND), U6.10 (GND), U7.1, U7.2, U7.7 (GND), U7.13, U8.7 (GND), U8.12, U8.13, U9.10 (GND), U10.8 (GND), U10.13 (A1), U10.14 (A0), U10.15 (E), U11.10 (GND), U12.7 (GND), U13.14 (GND), U13.20 (~CE), U14.23 (GND)
unnamed: R1.2, U6.1 (~Mr), U9.1 (~Mr)
unnamed: R2.2, U2.1, U2.2, U2.3
unnamed: U1.8, U14.3 (RST)
unnamed: U1.10, U7.10
unnamed: U1.11, U7.6
unnamed: U1.12, U12.6 (~CS~)
unnamed: U1.13, U7.8
unnamed: U2.8, U7.9
unnamed: U3.6, U4.10
unnamed: U3.8, U5.2
unnamed: U3.9, U4.8
unnamed: U3.10, U4.6
unnamed: U3.11, U4.12
unnamed: U5.6, U7.3
unnamed: U5.8, U7.4
unnamed: U5.11, U6.11 (Cp)
unnamed: U7.11, U8.3
unnamed: U8.6, U9.11 (Cp)
unnamed: U5.3, U10.1 (E)
unnamed: U8.5, U10.5 (O1)
unnamed: U5.12, U10.6 (O2)
unnamed: U8.9, U10.7 (O3)
unnamed: U8.8, U11.19 (G2), U13.22 (~OE)
unnamed: U12.1 (PA3), U14.A5
unnamed: U12.2 (PA2), U14.A4
unnamed: U12.3 (PA1), U14.20 (D17/A3)
unnamed: U12.4 (PA0), U14.19 (D16/A2)
unnamed: U12.10 (PC7), U14.17 (D14/A0)
unnamed: U12.16 (PC2), U14.18 (D15/A1)
unnamed: U12.18 (PB0), U14.5 (D2)
unnamed: U12.19 (PB1), U14.6 (~~D3)
unnamed: U12.20 (PB2), U14.7 (D4)
unnamed: U12.21 (PB3), U14.8 (~~D5)
unnamed: U12.22 (PB4), U14.9 (~~D6)
unnamed: U12.23 (PB5), U14.10 (D7)
unnamed: U12.24 (PB6), U14.11 (D8)
unnamed: U12.25 (PB7), U14.12 (~~D9)

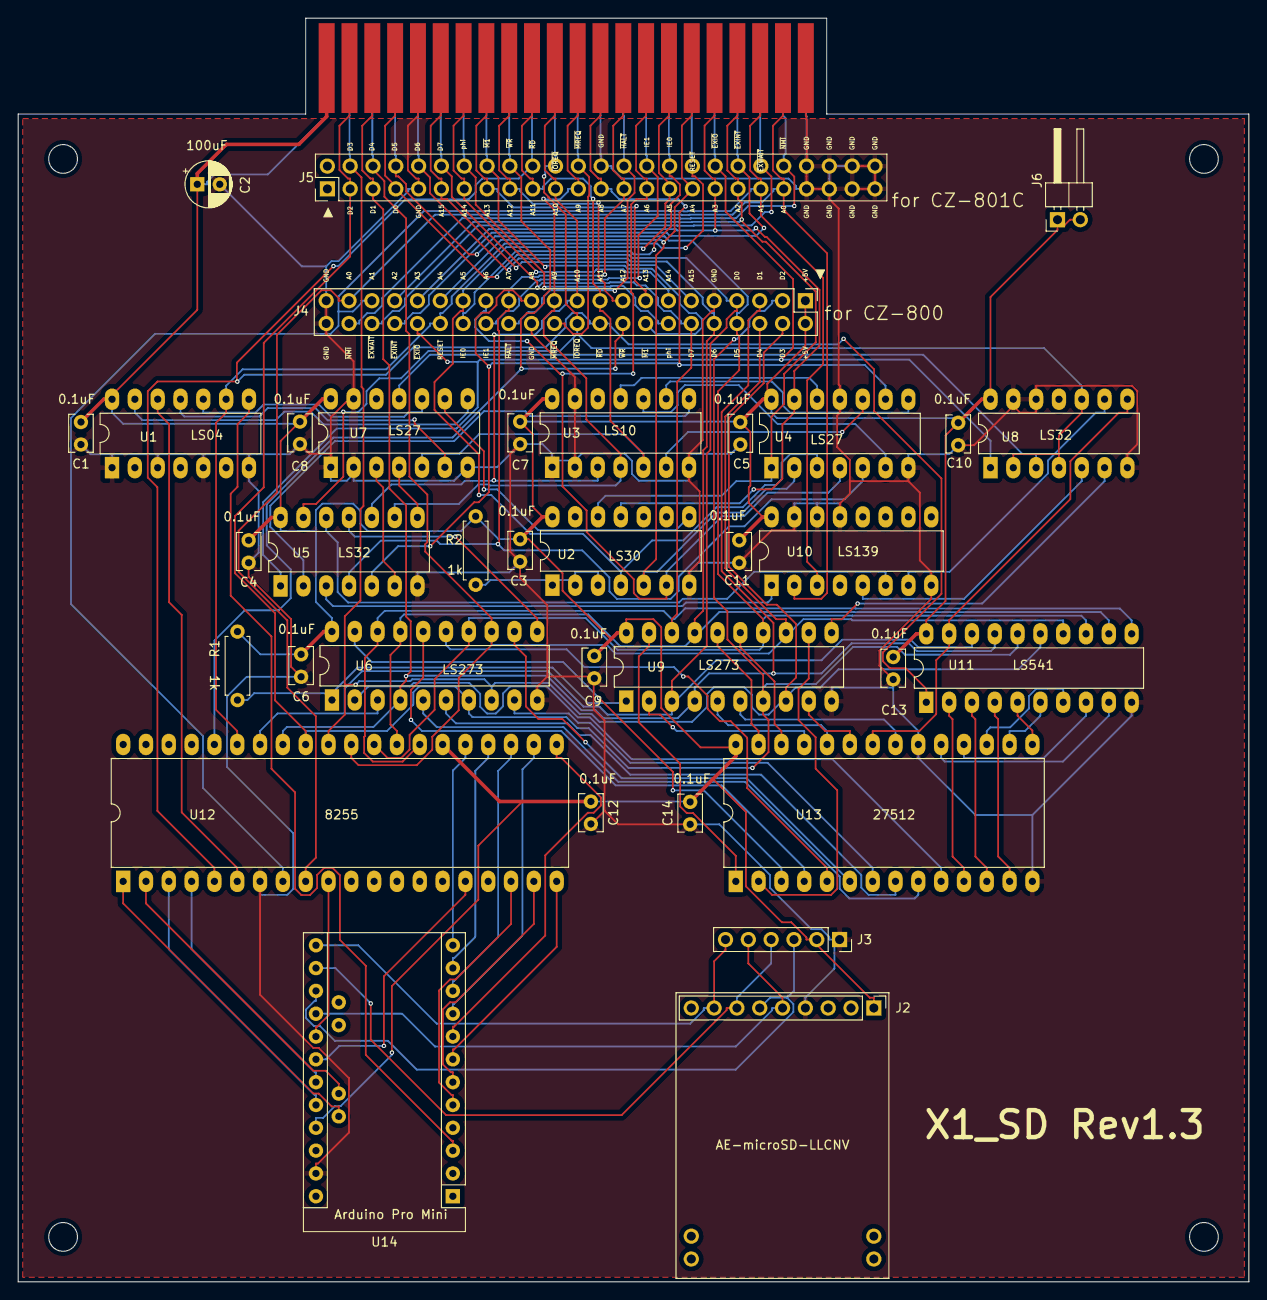
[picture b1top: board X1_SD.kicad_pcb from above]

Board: 2 copper layers, 137.0 x 140.7 mm, 40 parts (0 on the bottom side), 105 nets.

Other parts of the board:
MH1, MH2, MH3, MH4: MountingHole_3.2mm_M3
